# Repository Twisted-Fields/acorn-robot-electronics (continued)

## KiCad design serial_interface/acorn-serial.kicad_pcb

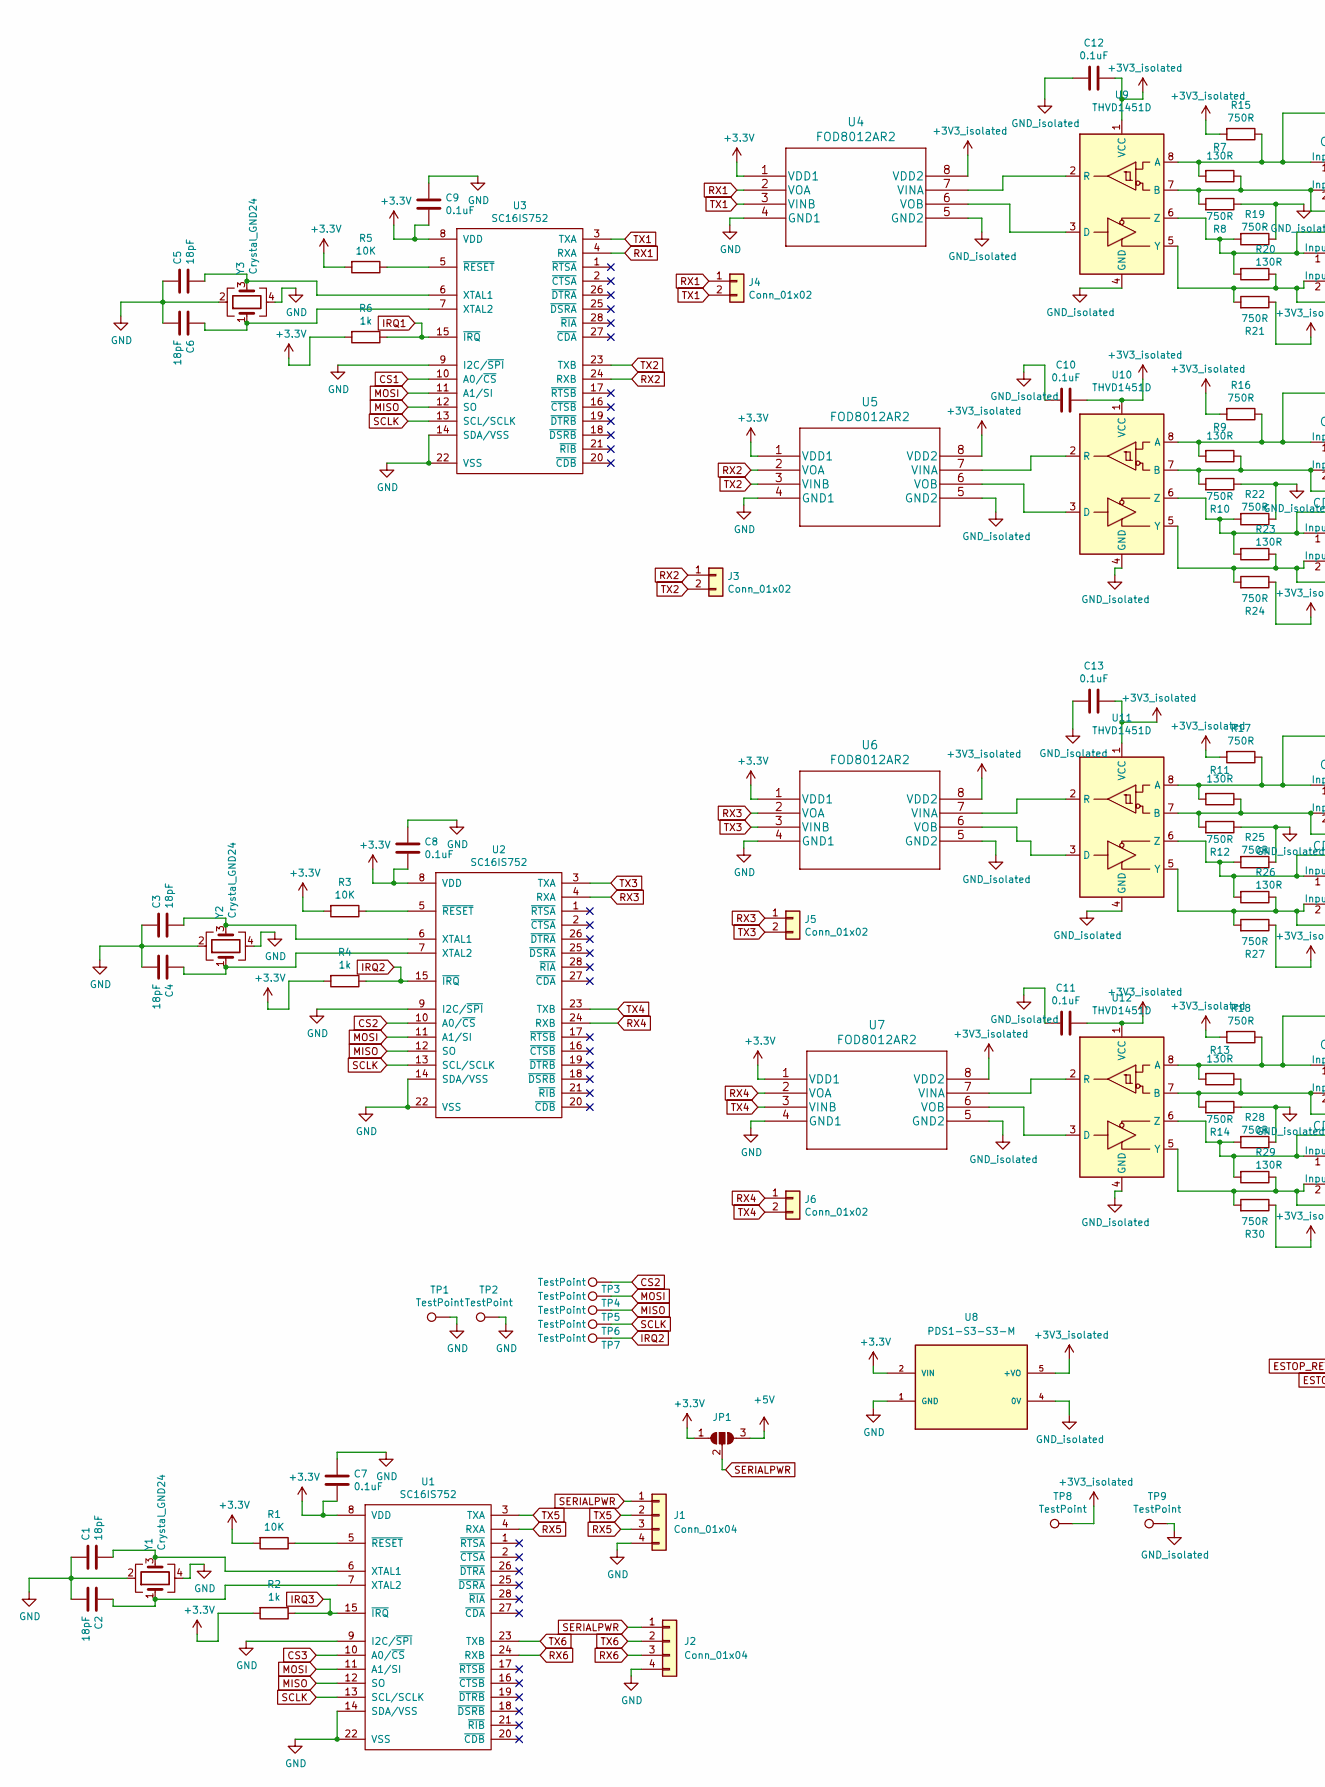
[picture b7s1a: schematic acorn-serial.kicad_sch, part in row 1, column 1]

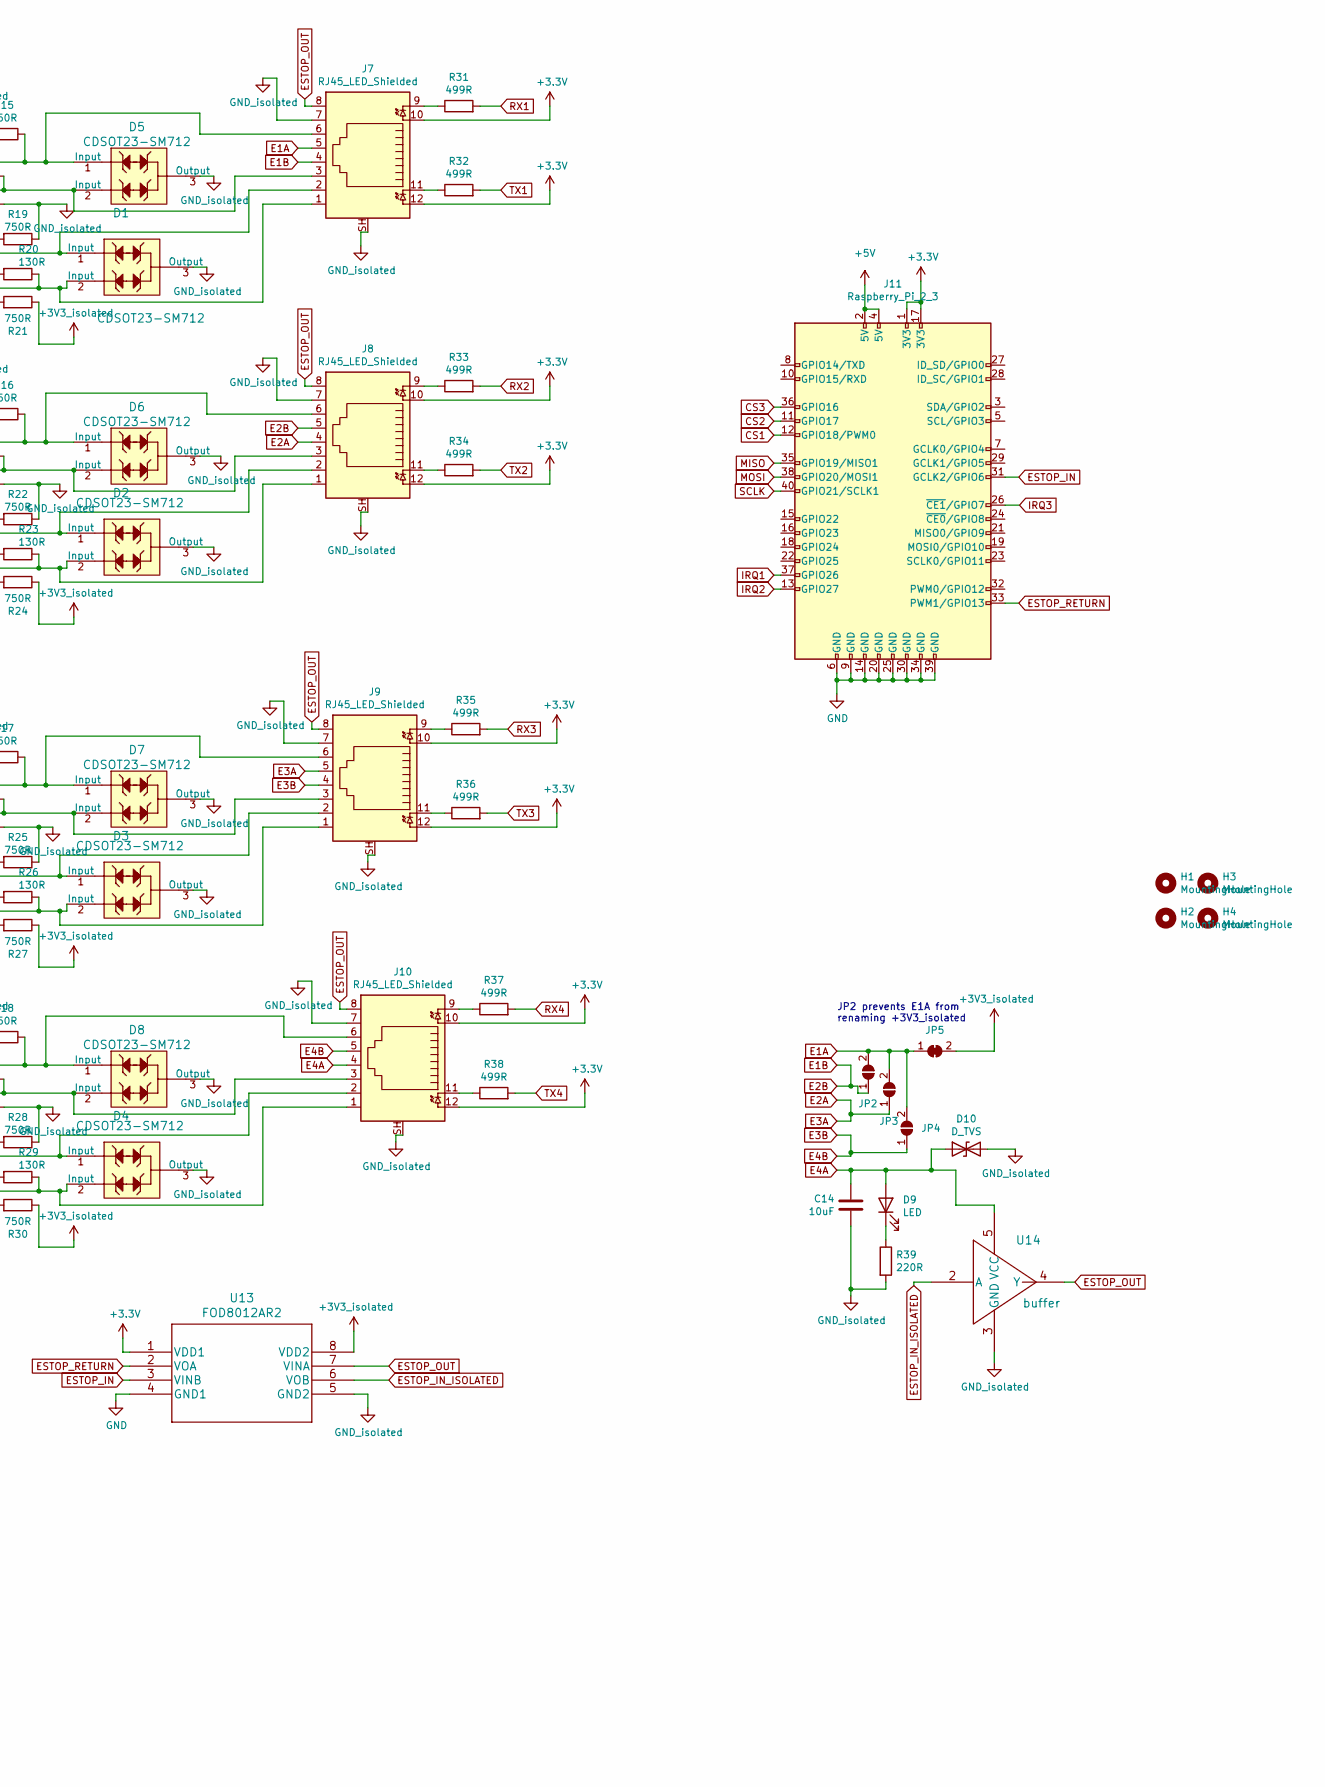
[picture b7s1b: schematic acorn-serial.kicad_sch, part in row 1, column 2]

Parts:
C1, C2, C3, C4, C5, C6: 18pF; C_0805_2012Metric; Digikey 311-1102-1-ND
C7, C8, C9, C11, C13: 0.1uF; C_0805_2012Metric; Digikey 311-1361-1-ND
C10, C12: 0.1uF; C_0805_2012Metric
C14: 10uF; C_0805_2012Metric; Digikey 311-1355-1-ND
D1, D2, D3, D4, D5, D6, D7, D8: CDSOT23-SM712; SOT-23-3; MPN CDSOT23-SM712; Digikey CDSOT23-SM712CT-ND
D9: LED; LED_1206_3216Metric; Digikey 160-1405-1-ND
D10: D_TVS; D_SOD-323; MPN DESD5V0U1BA-7; Digikey DESD5V0U1BA-7DICT-ND
H1, H2, H3, H4: MountingHole; MountingHole_3.7mm
J1, J2: Conn_01x04; Molex_KK-254_AE-6410-04A_1x04_P2.54mm_Vertical; Digikey WM4202-ND
J3, J4, J5, J6: Conn_01x02; PinHeader_1x02_P2.54mm_Vertical
J7, J8, J9, J10: RJ45_LED_Shielded; RJHSE-3381; Digikey RJHSE-3381-ND
J11: Raspberry_Pi_2_3; PinSocket_2x20_P2.54mm_Vertical; Digikey S2012E-20-ND
JP1: SolderJumper_3_Open; SolderJumper-3_P1.3mm_Open_RoundedPad1.0x1.5mm
JP2, JP3, JP4: SolderJumper_2_Open; SolderJumper-2_P1.3mm_Open_RoundedPad1.0x1.5mm
JP5: SolderJumper_2_Bridged; SolderJumper-2_P1.3mm_Bridged_Pad1.0x1.5mm
R1, R3, R5: 10K; R_0805_2012Metric; Digikey 311-10.0KCRCT-ND
R2, R4, R6: 1k; R_0805_2012Metric; Digikey 311-1.0KARCT-ND
R7, R9, R11, R13, R20, R23, R26, R29: 130R; R_0805_2012Metric; Digikey RMCF0805FT130RCT-ND
R8, R12, R14, R15, R17, R18, R19, R21, R25, R27, R28, R30: 750R; R_0805_2012Metric; Digikey RMCF0805FT750RCT-ND
R10, R16, R22, R24: 750R; R_0805_2012Metric
R31, R32, R33, R34, R35, R36, R37, R38: 499R; R_0805_2012Metric; Digikey 311-499CRCT-ND
R39: 220R; R_0805_2012Metric; Digikey A129741CT-ND
TP1, TP2, TP3, TP4, TP5, TP6, TP7, TP8, TP9: TestPoint; TestPoint_Keystone_5015_Micro-Minature; Digikey 36-5015CT-ND
U1, U2, U3: SC16IS752; TSSOP-28_4.4x9.7mm_P0.65mm; Digikey 568-4021-5-ND
U4, U5, U6, U7, U13: FOD8012AR2; Digikey FOD8012A-ND
U8: PDS1-S3-S3-M; CONV_PDS1-S3-S3-M; MPN PDS1-S3-S3-M; Digikey 102-5720-ND
U9, U10, U11, U12: THVD1451D; SOIC-8_3.9x4.9mm_P1.27mm; Digikey MAX3490EESA+CT-ND
U14: buffer; SOT-353_SC-70-5; MPN TC7SH34FU,LJ(CT; Digikey TC7SH34FULJ(CTCT-ND
Y1, Y2, Y3: Crystal_GND24; Crystal_SMD_Abracon_ABM3C-4Pin_5.0x3.2mm; Digikey 535-11286-1-ND

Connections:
+3V3: C7.2, C8.2, C9.2, J7.10, J7.12, J8.10, J8.12, J9.10, J9.12, J10.10, J10.12, J11.1 (3V3), J11.17 (3V3), JP1.1 (A), R1.2, R2.2, R3.2, R4.2, R5.2, R6.2, U1.8 (VDD), U2.8 (VDD), U3.8 (VDD), U4.1 (VDD1), U5.1 (VDD1), U6.1 (VDD1), U7.1 (VDD1), U8.2 (VIN), U13.1 (VDD1)
+3V3_isolated: C10.1, C11.1, C12.1, C13.1, JP5.2 (B), R15.2, R16.2, R17.2, R18.2, R21.1, R24.1, R27.1, R30.1, TP8.1, U4.8 (VDD2), U5.8 (VDD2), U6.8 (VDD2), U7.8 (VDD2), U8.5 (+VO), U9.1 (VCC), U10.1 (VCC), U11.1 (VCC), U12.1 (VCC), U13.8 (VDD2)
+5V: J11.2 (5V), J11.4 (5V), JP1.3 (B)
CS1: J11.12 (GPIO18/PWM0), U3.10 (A0/~CS)
CS2: J11.11 (GPIO17), TP3.1, U2.10 (A0/~CS)
CS3: J11.36 (GPIO16), U1.10 (A0/~CS)
E1A: J7.5, JP2.2 (B), JP3.2 (B), JP4.2 (B), JP5.1 (A)
E1B: J7.4, J8.5, JP2.1 (A)
E2A: J8.4, J9.5, JP3.1 (A)
E3B: J9.4, J10.5, JP4.1 (A)
E4A: C14.2, D9.2 (A), D10.1 (A1), J10.4, U14.5 (VCC)
ESTOP_IN: J11.31 (GCLK2/GPIO6), U13.3 (VINB)
ESTOP_IN_ISOLATED: U13.6 (VOB), U14.2 (A)
ESTOP_OUT: J7.8, J8.8, J9.8, J10.8, U13.7 (VINA), U14.4 (Y)
ESTOP_RETURN: J11.33 (PWM1/GPIO13), U13.2 (VOA)
GND: C1.1, C2.2, C3.1, C4.2, C5.1, C6.2, C7.1, C8.1, C9.1, J1.4, J2.4, J11.6 (GND), J11.9 (GND), J11.14 (GND), J11.20 (GND), J11.25 (GND), J11.30 (GND), J11.34 (GND), J11.39 (GND), TP1.1, TP2.1, U1.9 (I2C/~SPI), U1.14 (SDA/VSS), U1.22 (VSS), U2.9 (I2C/~SPI), U2.14 (SDA/VSS), U2.22 (VSS), U3.9 (I2C/~SPI), U3.14 (SDA/VSS), U3.22 (VSS), U4.4 (GND1), U5.4 (GND1), U6.4 (GND1), U7.4 (GND1), U8.1 (GND), U13.4 (GND1), Y1.2, Y1.4, Y2.2, Y2.4, Y3.2, Y3.4
GND_isolated: C10.2, C11.2, C12.2, C13.2, C14.1, D1.3 (Output), D2.3 (Output), D3.3 (Output), D4.3 (Output), D5.3 (Output), D6.3 (Output), D7.3 (Output), D8.3 (Output), D10.2 (A2), J7.7, J7.SH, J8.7, J8.SH, J9.7, J9.SH, J10.7, J10.SH, R8.1, R10.1, R12.1, R14.1, R19.1, R22.1, R25.1, R28.1, R39.2, TP9.1, U4.5 (GND2), U5.5 (GND2), U6.5 (GND2), U7.5 (GND2), U8.4 (0V), U9.4 (GND), U10.4 (GND), U11.4 (GND), U12.4 (GND), U13.5 (GND2), U14.3 (GND)
IRQ1: J11.37 (GPIO26), R6.1, U3.15 (~IRQ)
IRQ2: J11.13 (GPIO27), R4.1, TP7.1, U2.15 (~IRQ)
IRQ3: J11.26 (~CE1/GPIO7), R2.1, U1.15 (~IRQ)
MISO: J11.35 (GPIO19/MISO1), TP5.1, U1.12 (SO), U2.12 (SO), U3.12 (SO)
MOSI: J11.38 (GPIO20/MOSI1), TP4.1, U1.11 (A1/SI), U2.11 (A1/SI), U3.11 (A1/SI)
unnamed: C1.2, U1.6 (XTAL1), Y1.3
unnamed: C2.1, U1.7 (XTAL2), Y1.1
unnamed: C3.2, U2.6 (XTAL1), Y2.3
unnamed: C4.1, U2.7 (XTAL2), Y2.1
unnamed: C5.2, U3.6 (XTAL1), Y3.3
unnamed: C6.1, U3.7 (XTAL2), Y3.1
unnamed: D1.1 (Input), J7.2, R19.2, R20.2, U9.6 (Z)
unnamed: D1.2 (Input), J7.1, R20.1, R21.2, U9.5 (Y)
unnamed: D2.1 (Input), J8.2, R22.2, R23.2, U10.6 (Z)
unnamed: D2.2 (Input), J8.1, R23.1, R24.2, U10.5 (Y)
unnamed: D3.1 (Input), J9.2, R25.2, R26.2, U11.6 (Z)
unnamed: D3.2 (Input), J9.1, R26.1, R27.2, U11.5 (Y)
unnamed: D4.1 (Input), J10.2, R28.2, R29.2, U12.6 (Z)
unnamed: D4.2 (Input), J10.1, R29.1, R30.2, U12.5 (Y)
unnamed: D5.1 (Input), J7.6, R7.2, R15.1, U9.8 (A)
unnamed: D5.2 (Input), J7.3, R7.1, R8.2, U9.7 (B)
unnamed: D6.1 (Input), J8.6, R9.2, R16.1, U10.8 (A)
unnamed: D6.2 (Input), J8.3, R9.1, R10.2, U10.7 (B)
unnamed: D7.1 (Input), J9.6, R11.2, R17.1, U11.8 (A)
unnamed: D7.2 (Input), J9.3, R11.1, R12.2, U11.7 (B)
unnamed: D8.1 (Input), J10.6, R13.2, R18.1, U12.8 (A)
unnamed: D8.2 (Input), J10.3, R13.1, R14.2, U12.7 (B)
unnamed: D9.1 (K), R39.1
unnamed: J7.9, R31.1
unnamed: J7.11, R32.1
unnamed: J8.9, R33.1
unnamed: J8.11, R34.1
unnamed: J9.9, R35.1
unnamed: J9.11, R36.1
unnamed: J10.9, R37.1
unnamed: J10.11, R38.1
unnamed: R1.1, U1.5 (~RESET)
unnamed: R3.1, U2.5 (~RESET)
unnamed: R5.1, U3.5 (~RESET)
unnamed: U4.6 (VOB), U9.3 (D)
unnamed: U4.7 (VINA), U9.2 (R)
unnamed: U5.7 (VINA), U10.2 (R)
unnamed: U5.6 (VOB), U10.3 (D)
unnamed: U6.7 (VINA), U11.2 (R)
unnamed: U6.6 (VOB), U11.3 (D)
unnamed: U7.7 (VINA), U12.2 (R)
unnamed: U7.6 (VOB), U12.3 (D)
RX1: J4.1, R31.2, U3.4 (RXA), U4.2 (VOA)
RX2: J3.1, R33.2, U3.24 (RXB), U5.2 (VOA)
RX3: J5.1, R35.2, U2.4 (RXA), U6.2 (VOA)
RX4: J6.1, R37.2, U2.24 (RXB), U7.2 (VOA)
RX5: J1.3, U1.4 (RXA)
RX6: J2.3, U1.24 (RXB)
SCLK: J11.40 (GPIO21/SCLK1), TP6.1, U1.13 (SCL/SCLK), U2.13 (SCL/SCLK), U3.13 (SCL/SCLK)
SERIALPWR: J1.1, J2.1, JP1.2 (C)
TX1: J4.2, R32.2, U3.3 (TXA), U4.3 (VINB)
TX2: J3.2, R34.2, U3.23 (TXB), U5.3 (VINB)
TX3: J5.2, R36.2, U2.3 (TXA), U6.3 (VINB)
TX4: J6.2, R38.2, U2.23 (TXB), U7.3 (VINB)
TX5: J1.2, U1.3 (TXA)
TX6: J2.2, U1.23 (TXB)

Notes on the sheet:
JP2 prevents E1A from renaming +3V3_isolated

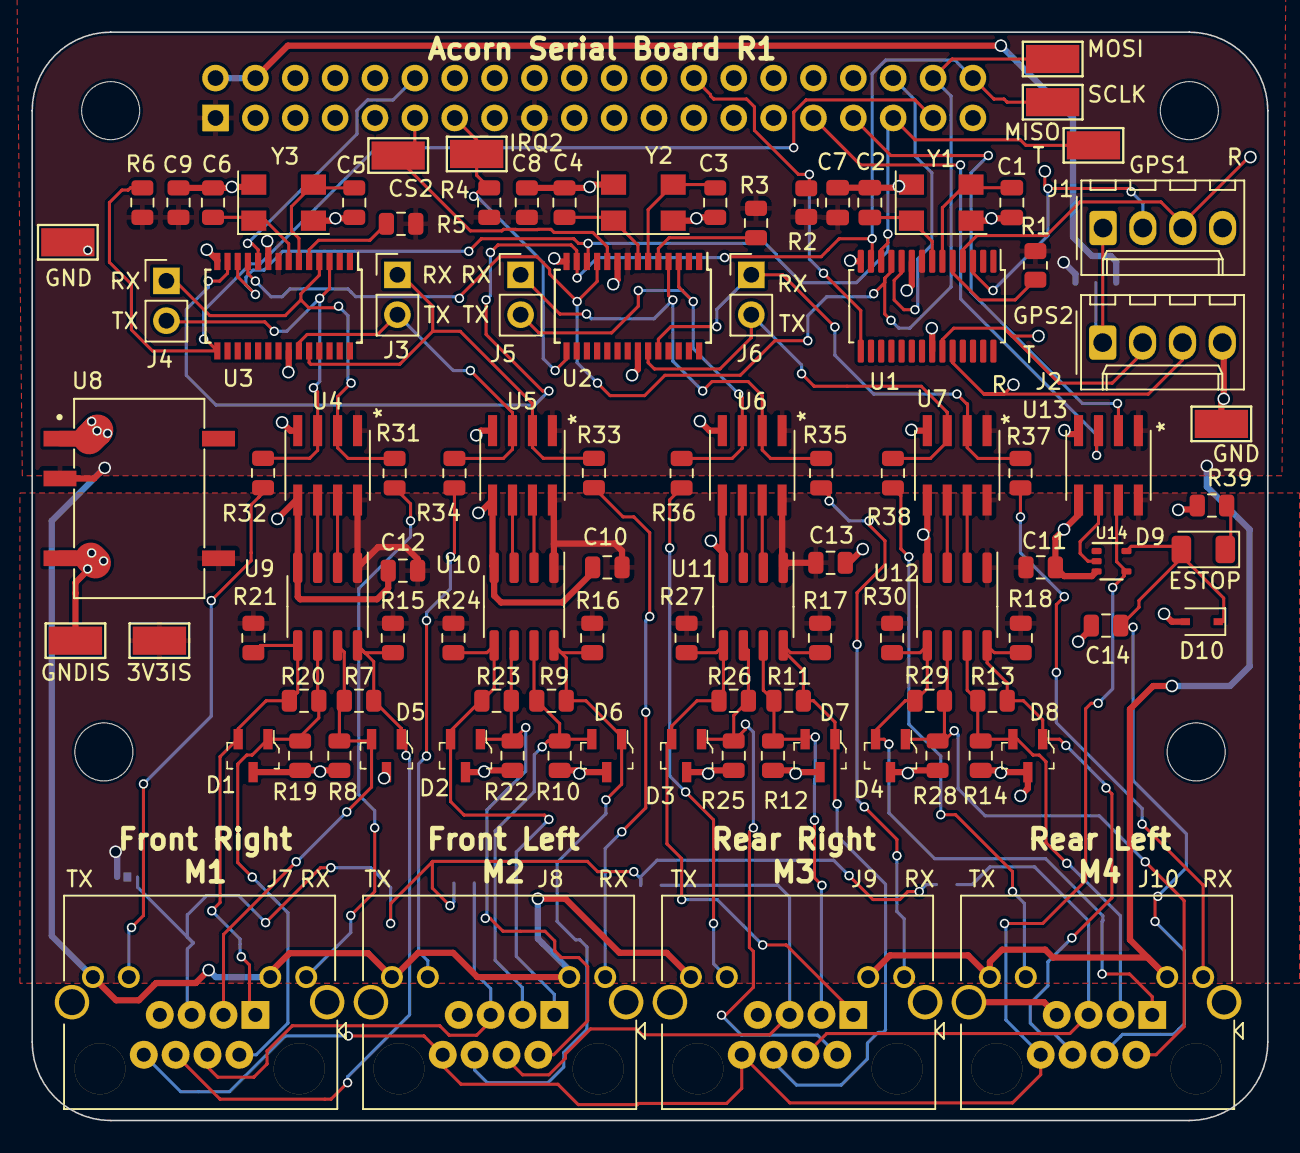
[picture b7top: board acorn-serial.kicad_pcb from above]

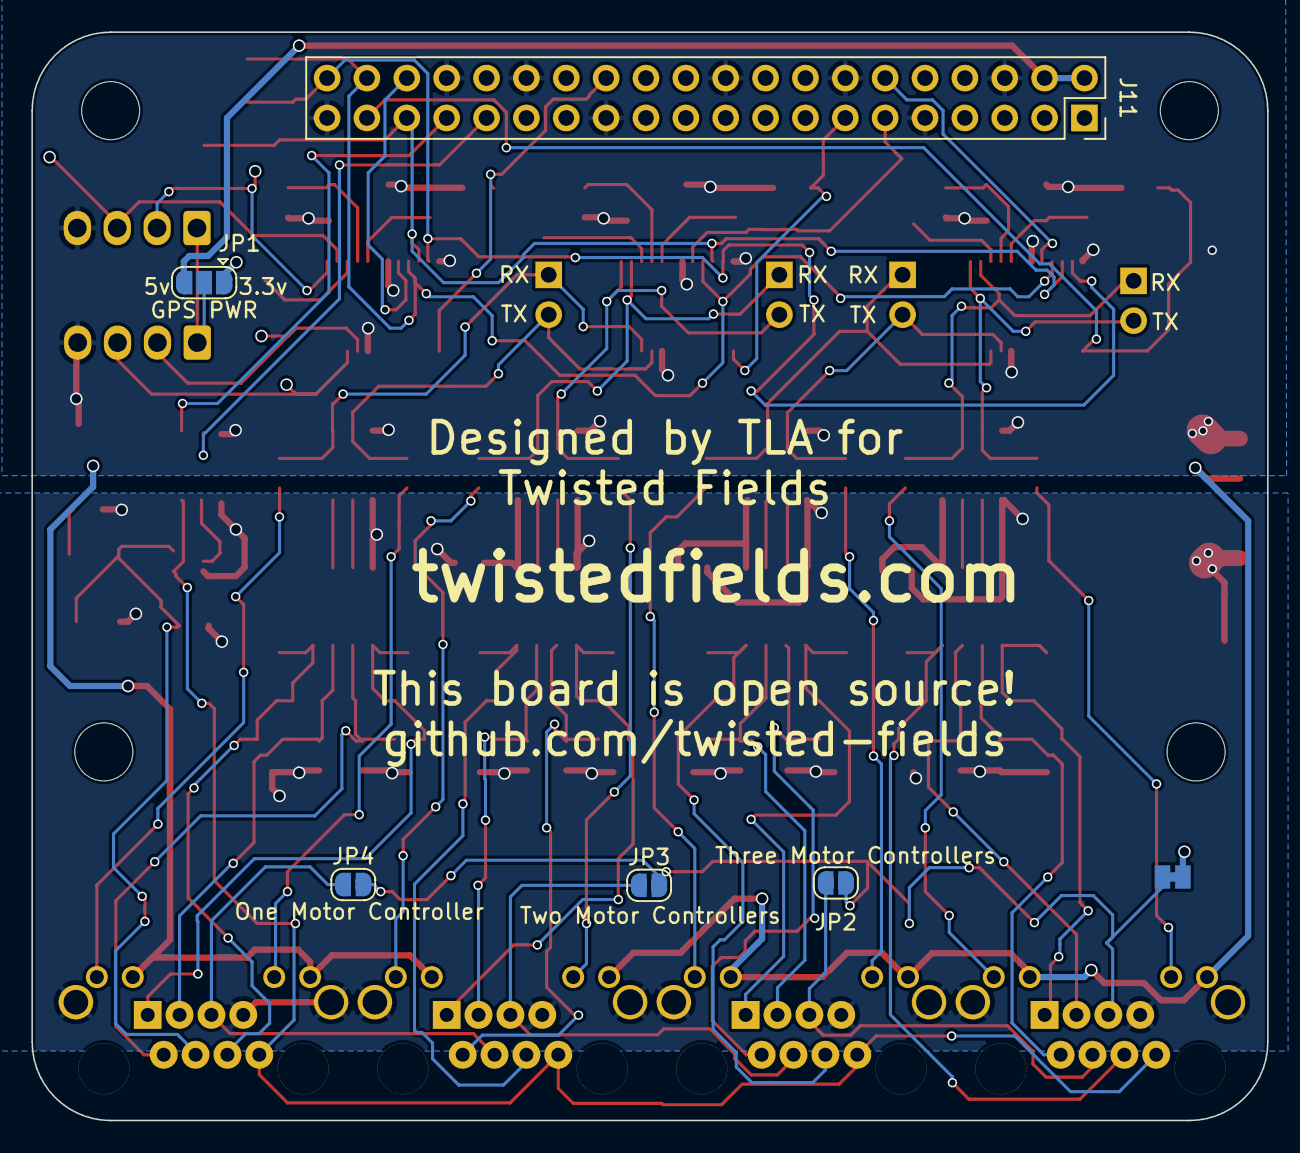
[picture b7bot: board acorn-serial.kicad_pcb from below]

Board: 2 copper layers, 78.7 x 69.3 mm, 109 parts (6 on the bottom side), 78 nets.

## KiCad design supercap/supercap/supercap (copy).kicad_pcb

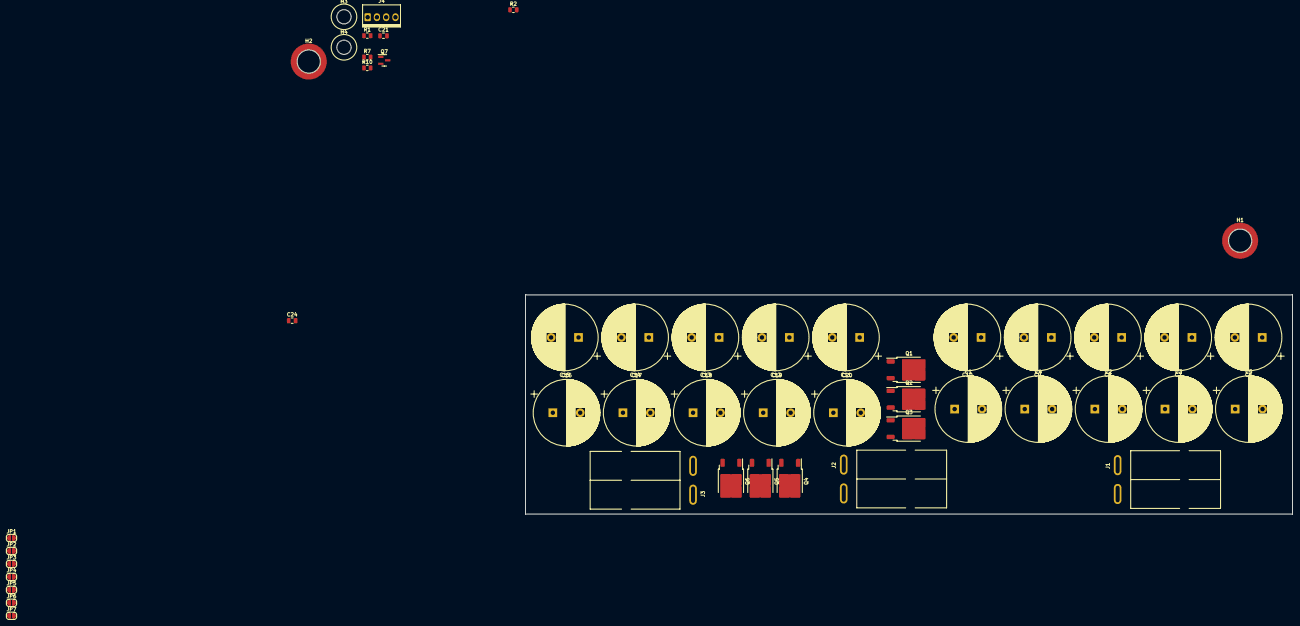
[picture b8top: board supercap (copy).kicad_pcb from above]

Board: 2 copper layers, 210.0 x 60.0 mm, 48 parts (0 on the bottom side), 27 nets, no tracks yet.

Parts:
C1, C2, C3, C4, C5, C6, C7, C8, C9, C10, C11, C12, C13, C14, C15, C16, C17, C18, C19, C20: 120F 2.3v; CP_Radial_D18.0mm_P7.50mm
C21, C24: 1uF; C_0805_2012Metric
H1, H2: MountingHole_Pad; Sinhoo-SMTSO40x-C2916378
H3, H4: MountingHole; MountingHole_3.9mm_Plastite_#6
J1, J2: Conn_01x02; PowerPole_PP45_1336G1_1x2_Horizontal
J3: Power Output; PowerPole_PP45_1336G1_1x2_Horizontal
J4: CAN2 PLUG; PINREX-744-81-04TW00 _1x04_P2.54mm_Vertical
JP1, JP2, JP3, JP4, JP5, JP6, JP7: SolderJumper_2_Open; SolderJumper-2_P1.3mm_Open_RoundedPad1.0x1.5mm
Q1, Q2, Q3, Q4, Q5, Q6: 100V 34A PMOS; TO-252-2
Q7: Q_NMOS_GSD; SOT-23
R1, R7: 10k; R_0805_2012Metric
R2, R10: 20k; R_0805_2012Metric

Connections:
+5V: J4.1, Q7.1 (G)
/VBUS_GATE: C21.1, Q1.1 (G), Q2.1 (G), Q3.1 (G), R1.2, R2.1
/VCAP_GATE: C24.1, Q4.1 (G), Q5.1 (G), Q6.1 (G), R7.2, R10.1
GND: C20.2, J1.2, J2.2, J3.2, J4.4, JP7.2 (B), Q7.2 (S), R2.2
unnamed: C1.2, C4.1
unnamed: C2.1, C4.2
unnamed: C2.2, C3.1
unnamed: C3.2, C5.1
unnamed: C5.2, C6.1
unnamed: C6.2, C7.1
unnamed: C7.2, C8.1
unnamed: C8.2, C9.1
unnamed: C9.2, C10.1
unnamed: C10.2, C11.1
unnamed: C11.2, C12.1
unnamed: C12.2, C13.1
unnamed: C13.2, C14.1
unnamed: C14.2, C15.1
unnamed: C15.2, C16.1
unnamed: C16.2, C17.1
unnamed: C17.2, C18.1
unnamed: C18.2, C19.1
unnamed: C19.2, C20.1
unnamed: JP7.1 (A), Q7.3 (D), R10.2
VBUS: C21.2, J1.1, J2.1, JP1.1 (A), JP2.1 (A), JP3.1 (A), Q1.3 (S), Q2.3 (S), Q3.3 (S), R1.1
VCAP: C1.1, C24.2, JP1.2 (B), JP2.2 (B), JP3.2 (B), JP4.1 (A), JP5.1 (A), JP6.1 (A), Q1.2 (D), Q2.2 (D), Q3.2 (D), Q4.3 (S), Q5.3 (S), Q6.3 (S), R7.1
VOUT: J3.1, JP4.2 (B), JP5.2 (B), JP6.2 (B), Q4.2 (D), Q5.2 (D), Q6.2 (D)

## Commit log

2021-02-03 Update readme formatting
2022-01-18 Add all updated boards for V2 system refresh
2022-03-01 Add photo of PCB to readme and doc folder
2022-11-24 add new JLCPCB assembled motherboard and archive old boards
2022-12-17 Update latest files for CM4 robot board. Ordered this version.
2022-12-17 Add post production notes
2022-12-17 Add magnetic homing sensor design files.
2023-01-06 Removed old photo from readme.
2023-01-27 Update docs with new picture and additional information on acorn.
2023-10-13 add supercap board
2023-10-25 Create kitspace.yaml
    https://kitspace.org/
    https://github.com/kitspace/kitspace#adding-your-project
2023-11-04 Rev 2 Supercap PCB, updates to Motherboard in progress
2023-11-18 CM4 robot board almost done for Rev 3.5
2024-01-18 Updated Motherboard design files to latest version.
2024-04-12 Update motherboard, in progress not complete
2024-04-26 Update motherboard and add soft start pcb
2024-05-06 Fix motherboard schematic page size
2024-05-31 Motherboard: Add GPS port and other updates. Ready for review.
2024-05-31 remove extra schematic notes
2024-07-11 update motherboard, add supercap_simple. ready for review
2024-07-12 move CM4 connector off board to fix DRC errors, exclude other errors as appropriate
2024-07-12 Resolve most of the schematic ERC errors.
2024-07-12 Clean up additional ERC warnings.
2024-07-13 Update with most design review feedback. Needs final checkout.
2024-08-03 Updated board files for July 2024 order. Added supercap_simple.
